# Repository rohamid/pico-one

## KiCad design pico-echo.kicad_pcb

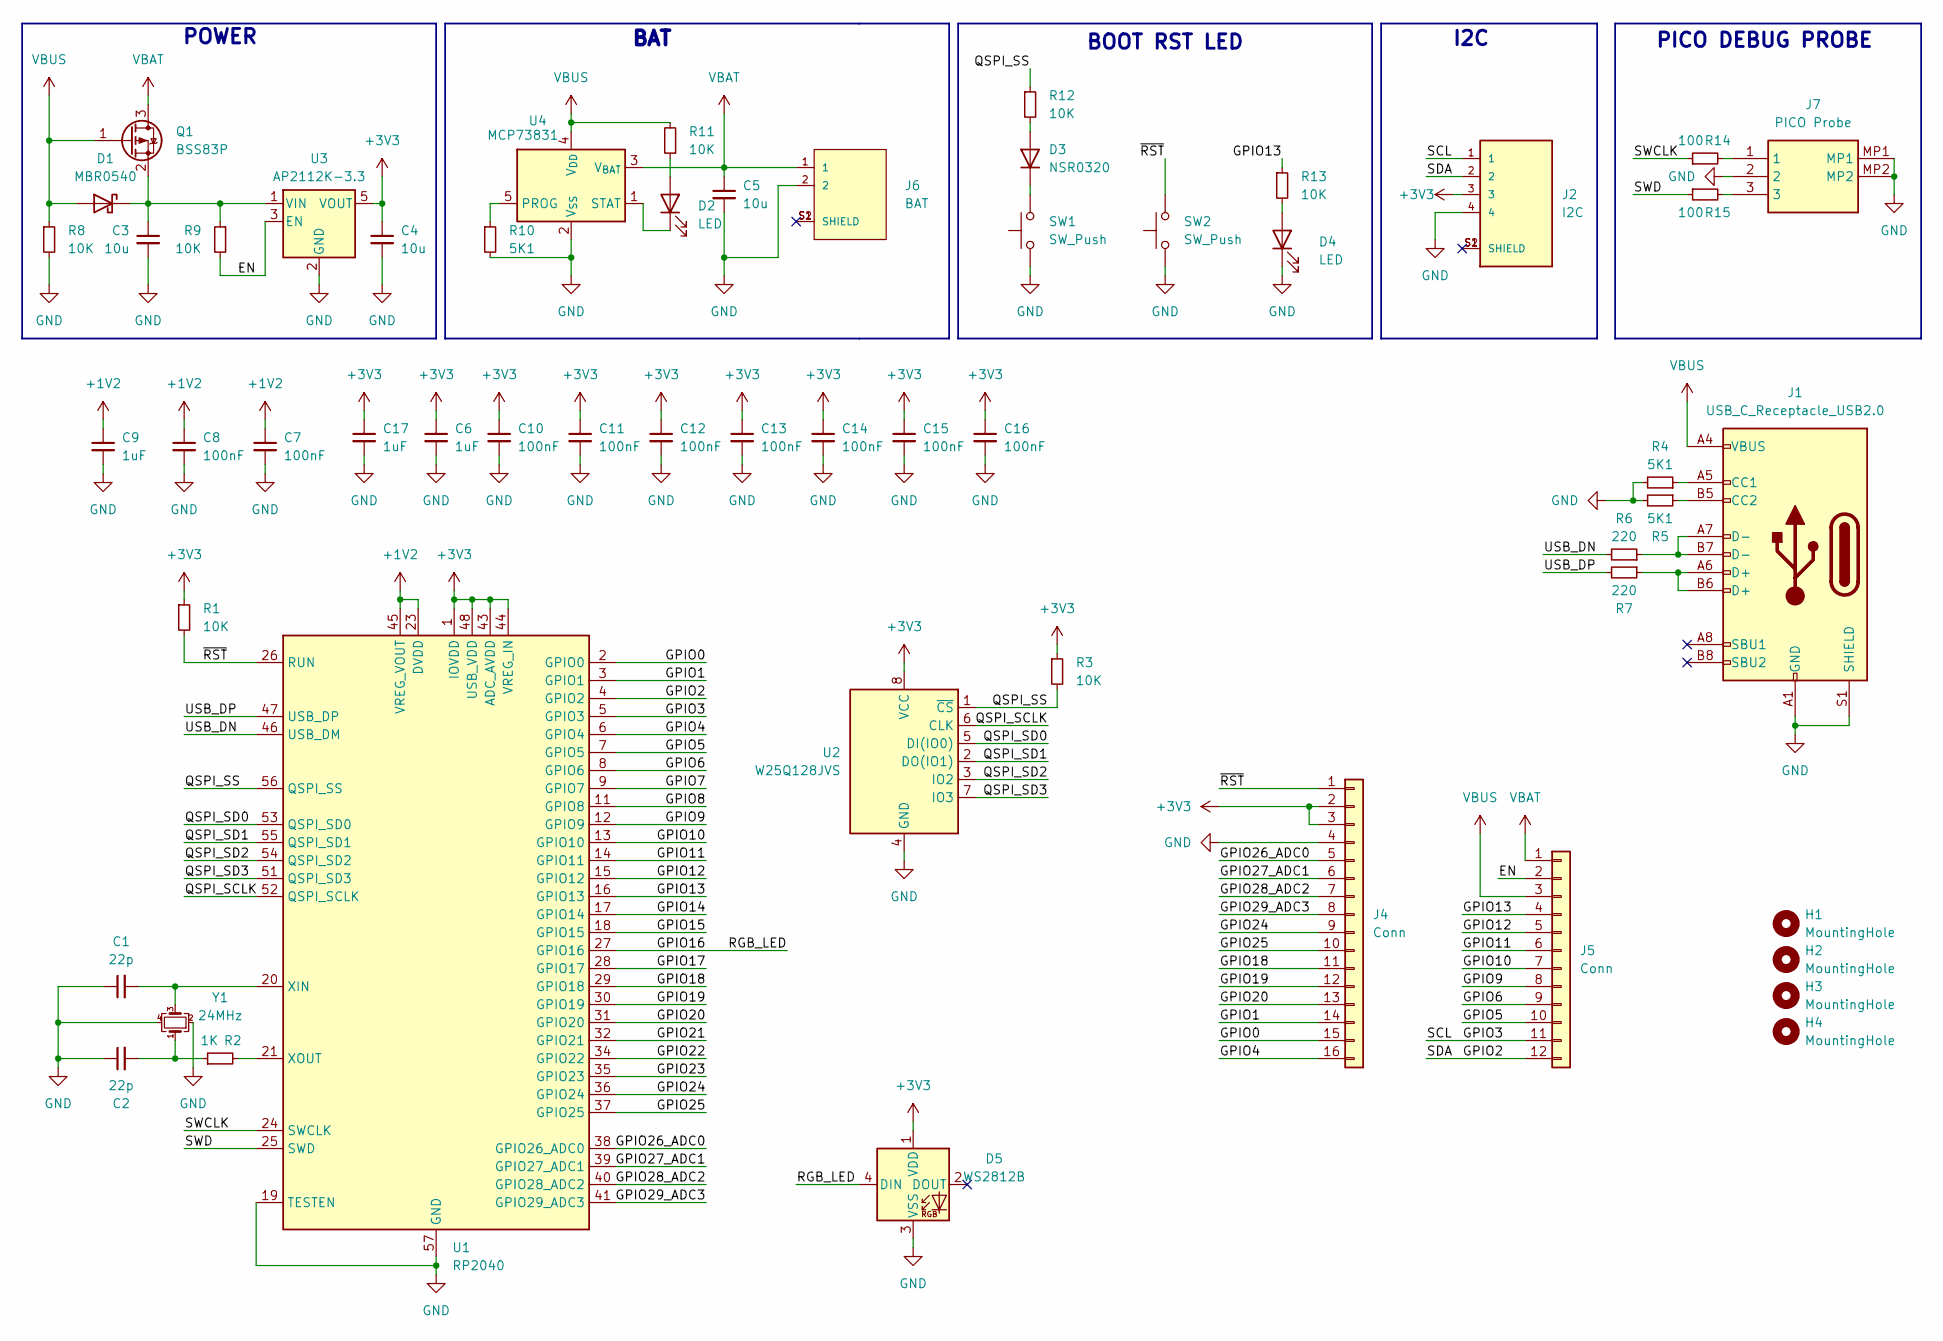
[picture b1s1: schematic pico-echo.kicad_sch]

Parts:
C1, C2: 22p; C_0402_1005Metric
C3, C4, C5: 10u; C_0603_1608Metric
C6, C9, C17: 1uF; C_0603_1608Metric
C7, C8, C10, C11, C12, C13, C14, C15, C16: 100nF; C_0402_1005Metric
D1: MBR0540; D_SOD-123
D2, D4: LED; LED_0603_1608Metric
D3: NSR0320; D_SOD-323_HandSoldering
D5: WS2812B; LED_SK6805_PLCC4_2.4x2.7mm_P1.3mm
H1, H2, H3, H4: MountingHole; MountingHole_2.5mm
J1: USB_C_Receptacle_USB2.0; USB_C_Receptacle_G-Switch_GT-USB-7010ASV
J2: I2C; JST_SM04B-SRSS-TB_LF__SN_
J4: Conn; PinHeader_1x16_P2.54mm_Vertical
J5: Conn; PinHeader_1x12_P2.54mm_Vertical
J6: BAT; JST_S2B-PH-SM4-TB_LF__SN_
J7: PICO Probe; BM03BSRSSTBTLFSN; Manufacturer_Part_Number BM03B-SRSS-TBT(LF)(SN)
Q1: BSS83P; SOT-23
R1, R3, R8, R9, R11, R12, R13: 10K; R_0402_1005Metric
R2: 1K; R_0402_1005Metric
R4, R5, R10: 5K1; R_0402_1005Metric
R6, R7: 220; R_0402_1005Metric
R14, R15: 100; R_0402_1005Metric
SW1: SW_Push; SW_SPST_EVQP7C
SW2: SW_Push; SW_SPST_PTS810
U1: RP2040; QFN-56-1EP_7x7mm_P0.4mm_EP3.2x3.2mm
U2: W25Q128JVS; USON-8-3x4
U3: AP2112K-3.3; SOT-23-5
U4: MCP73831; SOT-23-5
Y1: 24MHz; Crystal_SMD_2520-4Pin_2.5x2.0mm

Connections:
+1V2: C7.1, C8.1, C9.1, U1.23 (DVDD), U1.45 (VREG_VOUT), U1.50 (DVDD)
+3V3: C4.1, C6.1, C10.1, C11.1, C12.1, C13.1, C14.1, C15.1, C16.1, C17.1, D5.1 (VDD), J2.3, J4.2, J4.3, R1.1, R3.1, U1.1 (IOVDD), U1.10 (IOVDD), U1.22 (IOVDD), U1.33 (IOVDD), U1.42 (IOVDD), U1.43 (ADC_AVDD), U1.44 (VREG_IN), U1.48 (USB_VDD), U1.49 (IOVDD), U2.8 (VCC), U3.5 (VOUT)
/EN: J5.2, R9.2, U3.3 (EN)
/GPIO0: J4.15, U1.2 (GPIO0)
/GPIO1: J4.14, U1.3 (GPIO1)
/GPIO2: J2.2, J5.12, U1.4 (GPIO2)
/GPIO3: J2.1, J5.11, U1.5 (GPIO3)
/GPIO4: J4.16, U1.6 (GPIO4)
/GPIO5: J5.10, U1.7 (GPIO5)
/GPIO6: J5.9, U1.8 (GPIO6)
/GPIO7: U1.9 (GPIO7)
/GPIO8: U1.11 (GPIO8)
/GPIO9: J5.8, U1.12 (GPIO9)
/GPIO10: J5.7, U1.13 (GPIO10)
/GPIO11: J5.6, U1.14 (GPIO11)
/GPIO12: J5.5, U1.15 (GPIO12)
/GPIO13: J5.4, R13.1, U1.16 (GPIO13)
/GPIO14: U1.17 (GPIO14)
/GPIO15: U1.18 (GPIO15)
/GPIO16: D5.4 (DIN), U1.27 (GPIO16)
/GPIO17: U1.28 (GPIO17)
/GPIO18: J4.11, U1.29 (GPIO18)
/GPIO19: J4.12, U1.30 (GPIO19)
/GPIO20: J4.13, U1.31 (GPIO20)
/GPIO21: U1.32 (GPIO21)
/GPIO22: U1.34 (GPIO22)
/GPIO23: U1.35 (GPIO23)
/GPIO24: J4.9, U1.36 (GPIO24)
/GPIO25: J4.10, U1.37 (GPIO25)
/GPIO26_ADC0: J4.5, U1.38 (GPIO26_ADC0)
/GPIO27_ADC1: J4.6, U1.39 (GPIO27_ADC1)
/GPIO28_ADC2: J4.7, U1.40 (GPIO28_ADC2)
/GPIO29_ADC3: J4.8, U1.41 (GPIO29_ADC3)
/QSPI_SCLK: U1.52 (QSPI_SCLK), U2.6 (CLK)
/QSPI_SD0: U1.53 (QSPI_SD0), U2.5 (DI(IO0))
/QSPI_SD1: U1.55 (QSPI_SD1), U2.2 (DO(IO1))
/QSPI_SD2: U1.54 (QSPI_SD2), U2.3 (IO2)
/QSPI_SD3: U1.51 (QSPI_SD3), U2.7 (IO3)
/QSPI_SS: R3.2, R12.1, U1.56 (QSPI_SS), U2.1 (~CS)
/SWCLK: R14.1, U1.24 (SWCLK)
/SWD: R15.1, U1.25 (SWD)
/USB_DN: R6.2, U1.46 (USB_DM)
/USB_DP: R7.2, U1.47 (USB_DP)
/~RST: J4.1, R1.2, SW2.2, U1.26 (RUN)
GND: C1.1, C2.1, C3.2, C4.2, C5.2, C6.2, C7.2, C8.2, C9.2, C10.2, C11.2, C12.2, C13.2, C14.2, C15.2, C16.2, C17.2, D4.1 (K), D5.3 (VSS), J1.A1 (GND), J1.A12 (GND), J1.B1 (GND), J1.B12 (GND), J1.S1 (SHIELD), J2.4, J4.4, J6.2, J7.2, J7.MP1, J7.MP2, R4.2, R5.2, R8.2, R10.2, SW1.1, SW2.1, U1.19 (TESTEN), U1.57 (GND), U2.4 (GND), U3.2 (GND), U4.2 (V_{SS}), Y1.2, Y1.4
unnamed: C2.2, R2.1, Y1.1
unnamed: C3.1, D1.1 (K), Q1.2 (S), R9.1, U3.1 (VIN)
unnamed: D2.2 (A), R11.1
unnamed: D2.1 (K), U4.1 (STAT)
unnamed: D3.2 (A), R12.2
unnamed: D3.1 (K), SW1.2
unnamed: D4.2 (A), R13.2
unnamed: J1.A5 (CC1), R4.1
unnamed: J1.B5 (CC2), R5.1
unnamed: J1.A6 (D+), J1.B6 (D+), R7.1
unnamed: J1.A7 (D-), J1.B7 (D-), R6.1
unnamed: J7.1, R14.2
unnamed: J7.3, R15.2
unnamed: C1.2, U1.20 (XIN), Y1.3
unnamed: R2.2, U1.21 (XOUT)
unnamed: R10.1, U4.5 (PROG)
VBAT: C5.1, J5.1, J6.1, Q1.3 (D), U4.3 (V_{BAT})
VBUS: D1.2 (A), J1.A4 (VBUS), J1.A9 (VBUS), J1.B4 (VBUS), J1.B9 (VBUS), J5.3, Q1.1 (G), R8.1, R11.2, U4.4 (V_{DD})

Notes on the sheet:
BAT
I2C
POWER
PICO DEBUG PROBE
BOOT RST LED

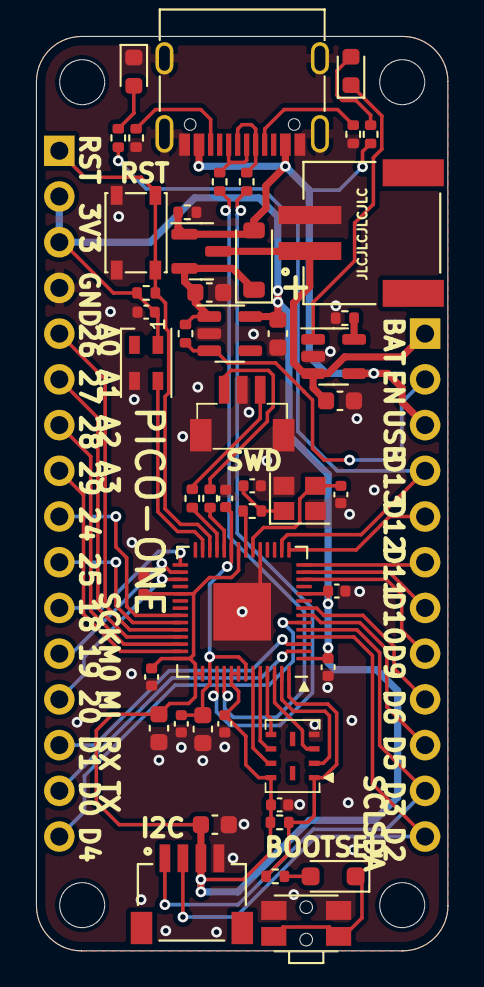
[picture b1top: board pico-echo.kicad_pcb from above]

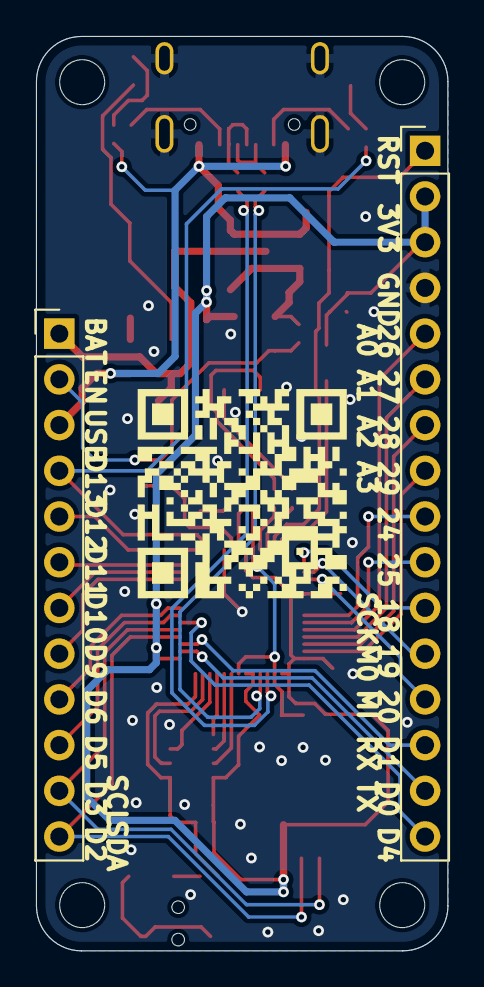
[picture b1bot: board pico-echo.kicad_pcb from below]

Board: 2 copper layers, 22.9 x 50.8 mm, 55 parts (2 on the bottom side), 55 nets.

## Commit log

2024-03-15 Updated tracks, not finished yet
2024-03-16 Add SWD conn, change Flash to USON, tracks almost finished
2024-03-17 Finished tracks
2024-03-18 Added github repo qrcode logo
2024-03-19 Updated .gitignore
2024-03-25 Add B.O.M to the schematic (not finished yet)
